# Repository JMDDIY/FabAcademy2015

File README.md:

# FabAcademy2015
'Homework' repository during FAB Academy 2015

if you want to have more information about those files, you should visit my webpage on the 
Fab Academy repository: http://fabacademy.org/archives/2015/eu/students/durney.jean-marie/index.html

All files here are based on Creative Commons
Attribution-NonCommercial-ShareAlike 4.0 International (CC BY-NC-SA 4.0)

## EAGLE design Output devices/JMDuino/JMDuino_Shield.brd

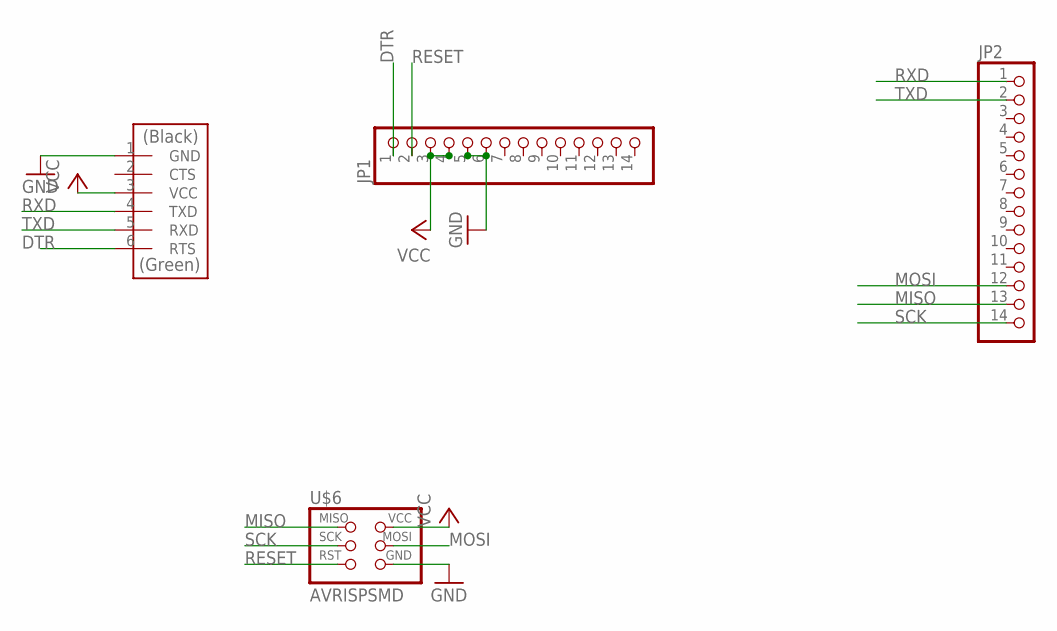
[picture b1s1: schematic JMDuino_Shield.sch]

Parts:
JP1, JP2: PINHD-1X14; 1X14
U$1: FTDI-SMD-HEADER; 1X06SMD
U$6: AVRISPSMD; 2X03SMD

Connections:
DTR: JP1.1, U$1.6 (RTS)
GND: JP1.5, JP1.6, U$1.1 (GND), U$6.6 (GND)
MISO: JP2.13, U$6.1 (MISO)
MOSI: JP2.12, U$6.4 (MOSI)
RESET: JP1.2, U$6.5 (RST)
RXD: JP2.1, U$1.4 (TXD)
SCK: JP2.14, U$6.3 (SCK)
TXD: JP2.2, U$1.5 (RXD)
VCC: JP1.3, JP1.4, U$1.3 (VCC), U$6.2 (VCC)

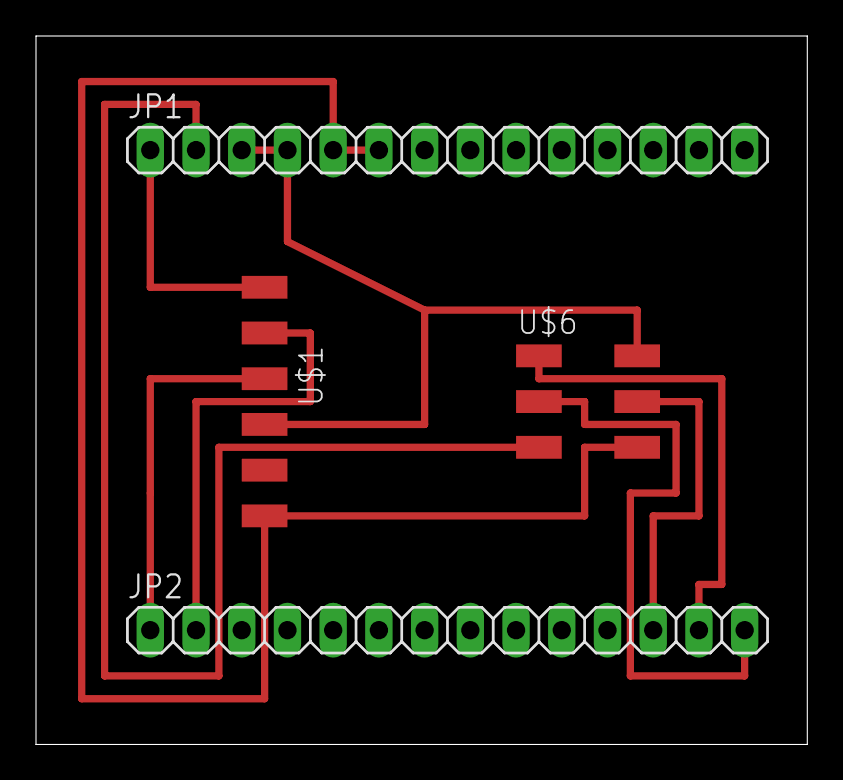
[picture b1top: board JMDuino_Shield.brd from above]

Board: 2 copper layers, 42.9 x 39.4 mm, 4 parts (0 on the bottom side), 9 nets.

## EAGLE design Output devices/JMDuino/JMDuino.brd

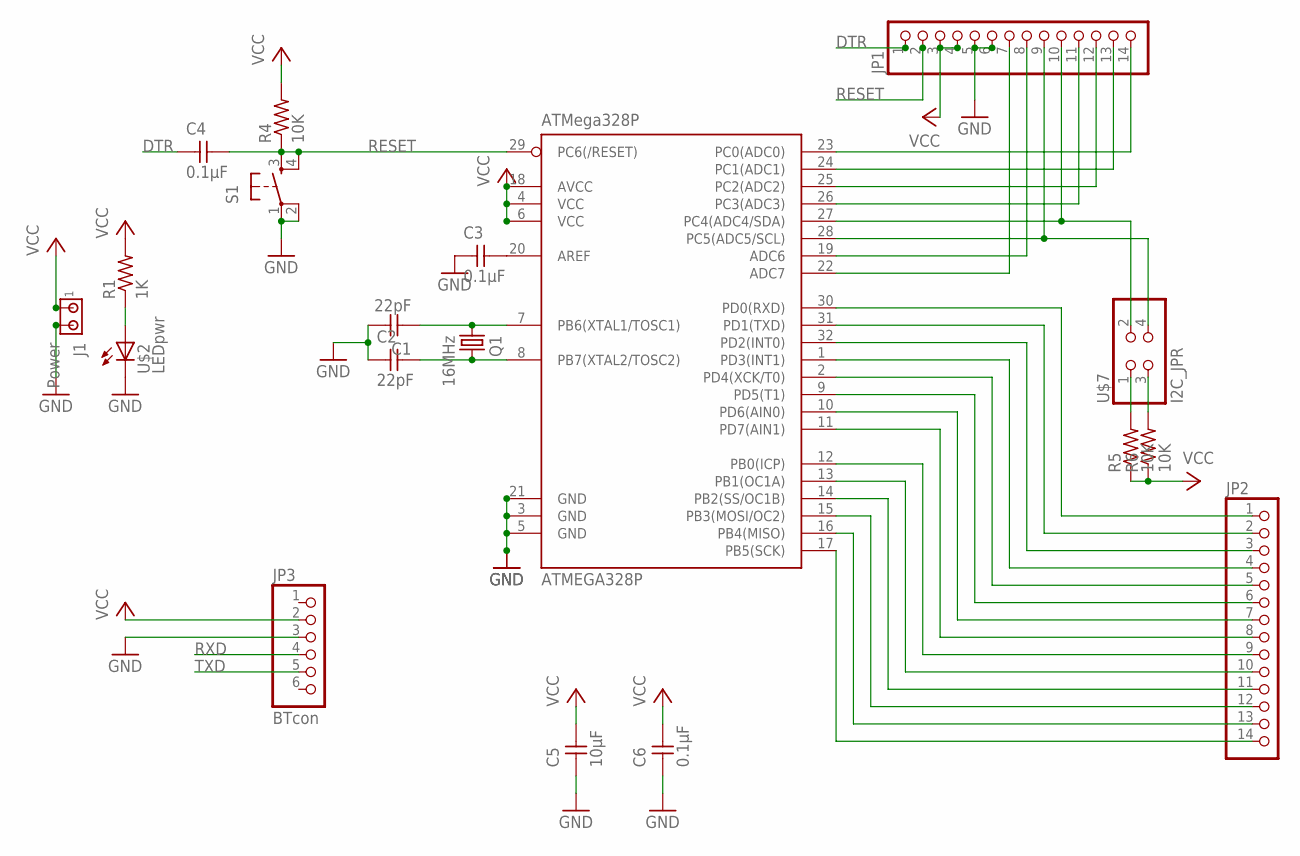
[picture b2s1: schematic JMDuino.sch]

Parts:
ATMEGA328P: ATMega328P; TQFP32-08THIN
C1, C2: 22pF; C1206FAB
C3, C4, C6: 0.1µF; C1206FAB
C5: 10µF; C1206FAB
J1: Power; 350428-1
JP1, JP2: PINHD-1X14; 1X14
JP3: BTcon; 1X06
Q1: 16MHz; 2-SMD-5X3MM
R1: 1K; R1206FAB
R4, R5, R6: 10K; R1206FAB
S1: 6MM_SWITCH6MM_SWITCH; 6MM_SWITCH
U$2: LEDpwr; LED1206FAB
U$7: I2C_JPR; 2X02SMD

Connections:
DTR: C4.1, JP1.1
GND: ATMEGA328P.3 (GND), ATMEGA328P.5 (GND), ATMEGA328P.21 (GND), C1.2, C2.1, C3.1, C5.1, C6.1, J1.2, JP1.5, JP1.6, JP3.3, S1.1, S1.2 (P1), U$2.2 (C)
MISO: ATMEGA328P.16 (PB4(MISO)), JP2.13
MOSI: ATMEGA328P.15 (PB3(MOSI/OC2)), JP2.12
unnamed: ATMEGA328P.23 (PC0(ADC0)), JP1.14
unnamed: ATMEGA328P.24 (PC1(ADC1)), JP1.13
unnamed: ATMEGA328P.25 (PC2(ADC2)), JP1.12
unnamed: ATMEGA328P.26 (PC3(ADC3)), JP1.11
unnamed: ATMEGA328P.20 (AREF), C3.2
unnamed: ATMEGA328P.27 (PC4(ADC4/SDA)), JP1.10, U$7.2
unnamed: ATMEGA328P.9 (PD5(T1)), JP2.6
unnamed: ATMEGA328P.28 (PC5(ADC5/SCL)), JP1.9, U$7.4
unnamed: ATMEGA328P.32 (PD2(INT0)), JP2.3
unnamed: ATMEGA328P.1 (PD3(INT1)), JP2.4
unnamed: ATMEGA328P.2 (PD4(XCK/T0)), JP2.5
unnamed: ATMEGA328P.10 (PD6(AIN0)), JP2.7
unnamed: ATMEGA328P.11 (PD7(AIN1)), JP2.8
unnamed: ATMEGA328P.12 (PB0(ICP)), JP2.9
unnamed: ATMEGA328P.13 (PB1(OC1A)), JP2.10
unnamed: ATMEGA328P.14 (PB2(SS/OC1B)), JP2.11
unnamed: R1.1, U$2.1 (A)
unnamed: R5.2, U$7.1
unnamed: ATMEGA328P.7 (PB6(XTAL1/TOSC1)), C1.1, Q1.P$1 (1)
unnamed: ATMEGA328P.8 (PB7(XTAL2/TOSC2)), C2.2, Q1.P$2 (2)
unnamed: ATMEGA328P.19 (ADC6), JP1.8
unnamed: R6.2, U$7.3
unnamed: ATMEGA328P.22 (ADC7), JP1.7
RESET: ATMEGA328P.29 (PC6(/RESET)), C4.2, JP1.2, R4.1, S1.4 (S1)
RXD: ATMEGA328P.30 (PD0(RXD)), JP2.1, JP3.4
SCK: ATMEGA328P.17 (PB5(SCK)), JP2.14
TXD: ATMEGA328P.31 (PD1(TXD)), JP2.2, JP3.5
VCC: ATMEGA328P.4 (VCC), ATMEGA328P.6 (VCC), ATMEGA328P.18 (AVCC), C5.2, C6.2, J1.1, JP1.3, JP1.4, JP3.2, R1.2, R4.2, R5.1, R6.1

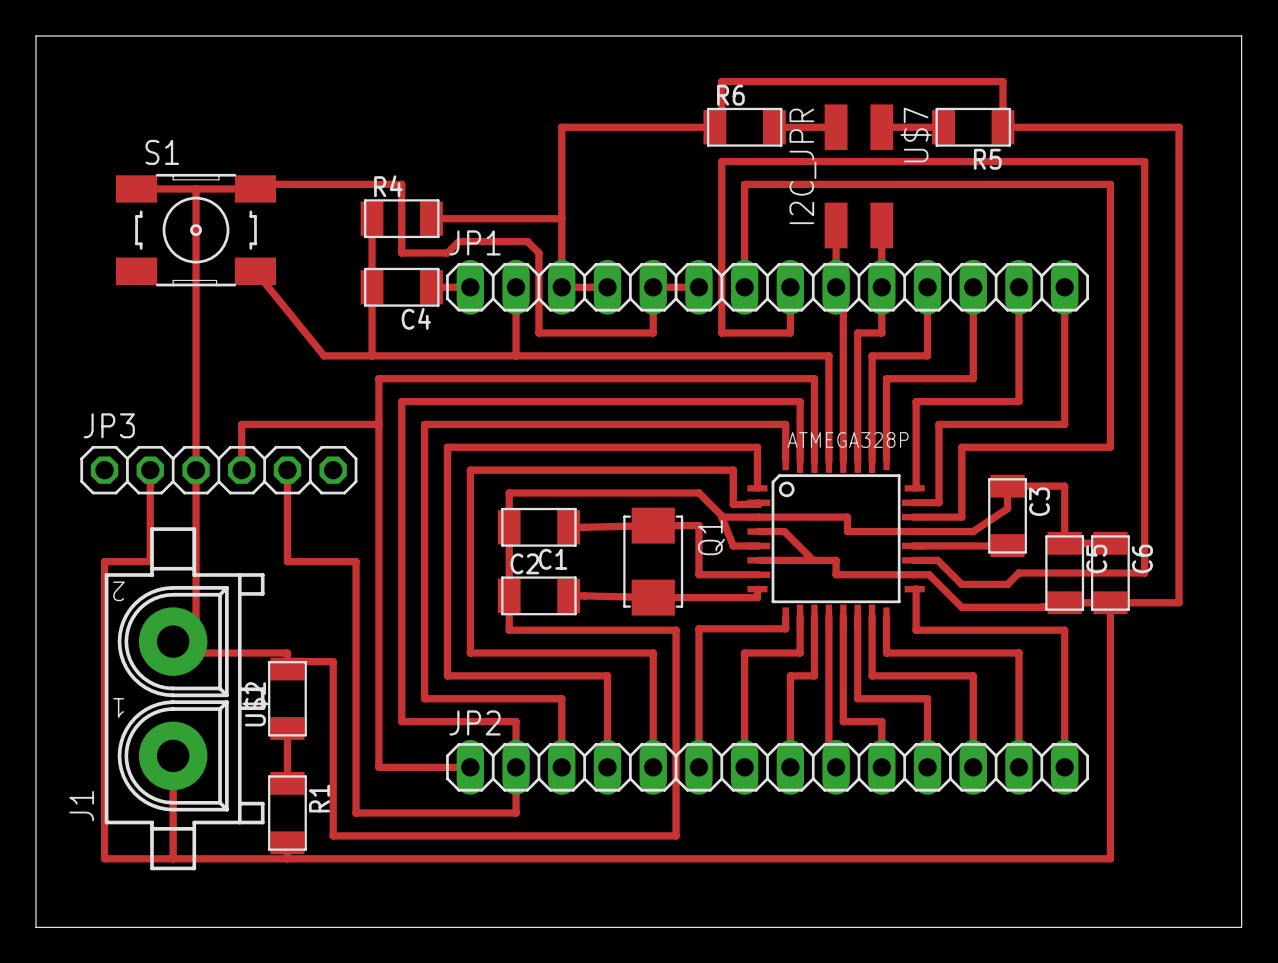
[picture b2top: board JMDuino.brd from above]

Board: 2 copper layers, 67.0 x 49.5 mm, 19 parts (0 on the bottom side), 32 nets.

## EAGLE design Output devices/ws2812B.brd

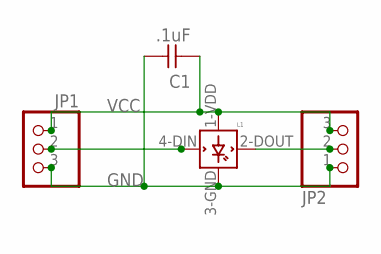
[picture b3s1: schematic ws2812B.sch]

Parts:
C1: .1uF; C1206FAB
JP1, JP2: PINHD-1X3CB; 1X03-CLEANBIG
L1: WS2812B

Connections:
GND: C1.2, JP1.3, JP2.1, L1.3-GND (GND)
unnamed: JP2.2, L1.2-DOUT (DOUT)
unnamed: JP1.2, L1.4-DIN (DIN)
VCC: C1.1, JP1.1, JP2.3, L1.1-VDD (VDD)

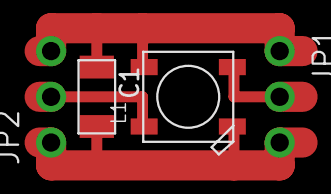
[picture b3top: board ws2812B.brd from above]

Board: 2 copper layers, 4 parts (0 on the bottom side), 4 nets.

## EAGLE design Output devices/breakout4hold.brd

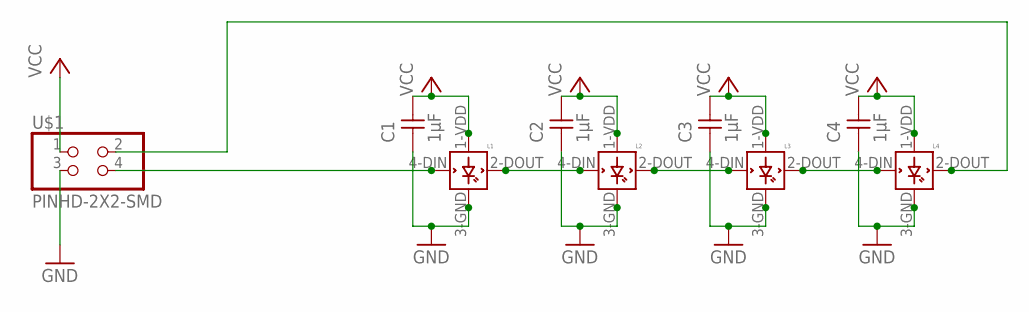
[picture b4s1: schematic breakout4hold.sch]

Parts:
C1, C2, C3, C4: 1µF; C1206FAB
L1, L2, L3, L4: WS2812B
U$1: PINHD-2X2-SMD; 2X02SMD

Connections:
GND: C1.1, C2.1, C3.1, C4.1, L1.3-GND (GND), L2.3-GND (GND), L3.3-GND (GND), L4.3-GND (GND), U$1.3
unnamed: L4.2-DOUT (DOUT), U$1.2
unnamed: L1.4-DIN (DIN), U$1.4
unnamed: L1.2-DOUT (DOUT), L2.4-DIN (DIN)
unnamed: L2.2-DOUT (DOUT), L3.4-DIN (DIN)
unnamed: L3.2-DOUT (DOUT), L4.4-DIN (DIN)
VCC: C1.2, C2.2, C3.2, C4.2, L1.1-VDD (VDD), L2.1-VDD (VDD), L3.1-VDD (VDD), L4.1-VDD (VDD), U$1.1

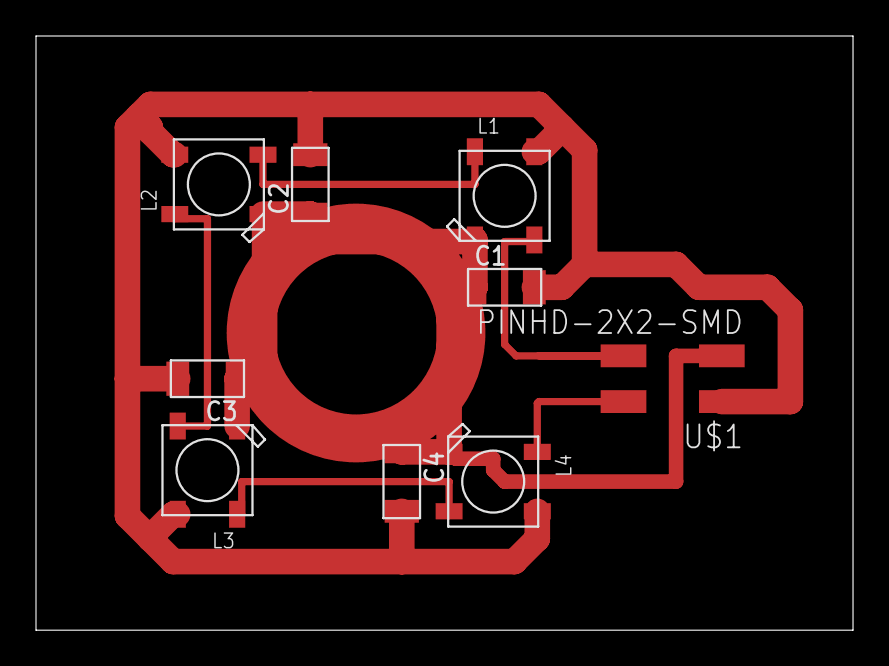
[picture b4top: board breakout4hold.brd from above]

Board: 2 copper layers, 45.4 x 33.0 mm, 9 parts (0 on the bottom side), 7 nets.

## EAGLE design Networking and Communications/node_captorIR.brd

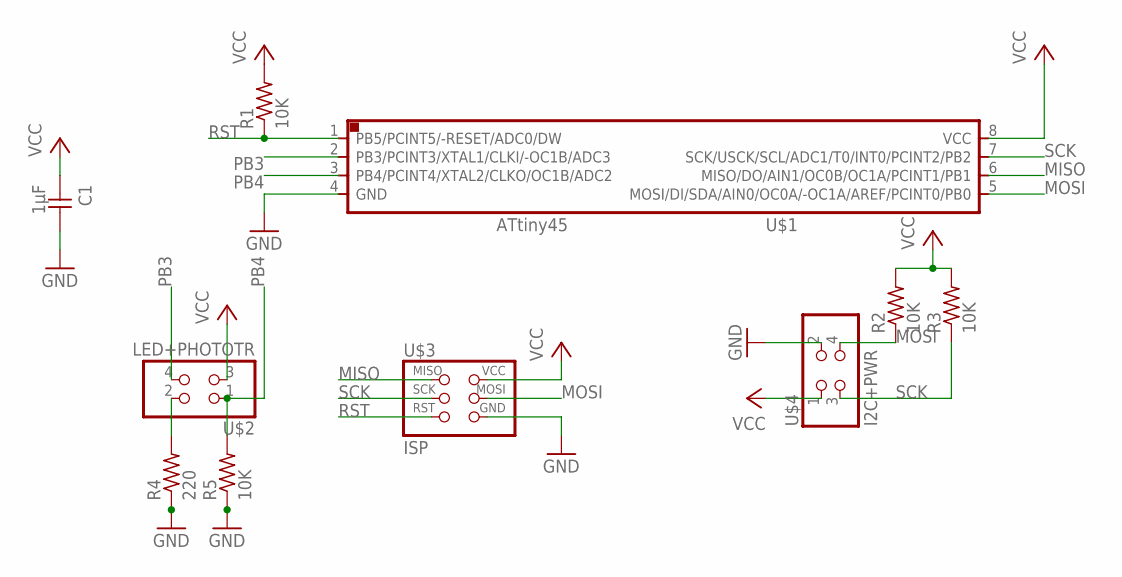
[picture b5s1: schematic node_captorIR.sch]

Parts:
C1: 1µF; C1206FAB
R1, R2, R3, R5: 10K; R1206FAB
R4: 220; R1206FAB
U$1: ATTINY45SI; SOIC8
U$2: LED+PHOTOTR; 2X02SMD
U$3: ISP; 2X03SMD
U$4: I2C+PWR; 2X02SMD

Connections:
GND: C1.2, R4.1, R5.1, U$1.4 (GND), U$3.6 (GND), U$4.2
MISO: U$1.6 (MISO/DO/AIN1/OC0B/OC1A/PCINT1/PB1), U$3.1 (MISO)
MOSI: R2.1, U$1.5 (MOSI/DI/SDA/AIN0/OC0A/-OC1A/AREF/PCINT0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), U$3.4 (MOSI), U$4.4
unnamed: R4.2, U$2.2
PB3: U$1.2 (PB3/PCINT3/XTAL1/CLKI/-OC1B/ADC3), U$2.4
PB4: R5.2, U$1.3 (PB4/PCINT4/XTAL2/CLKO/OC1B/ADC2), U$2.1
RST: R1.1, U$1.1 (PB5/PCINT5/-RESET/ADC0/DW), U$3.5 (RST)
SCK: R3.1, U$1.7 (SCK/USCK/SCL/ADC1/T0/INT0/PCINT2/PB2), U$3.3 (SCK), U$4.3
VCC: C1.1, R1.2, R2.2, R3.2, U$1.8 (VCC), U$2.3, U$3.2 (VCC), U$4.1

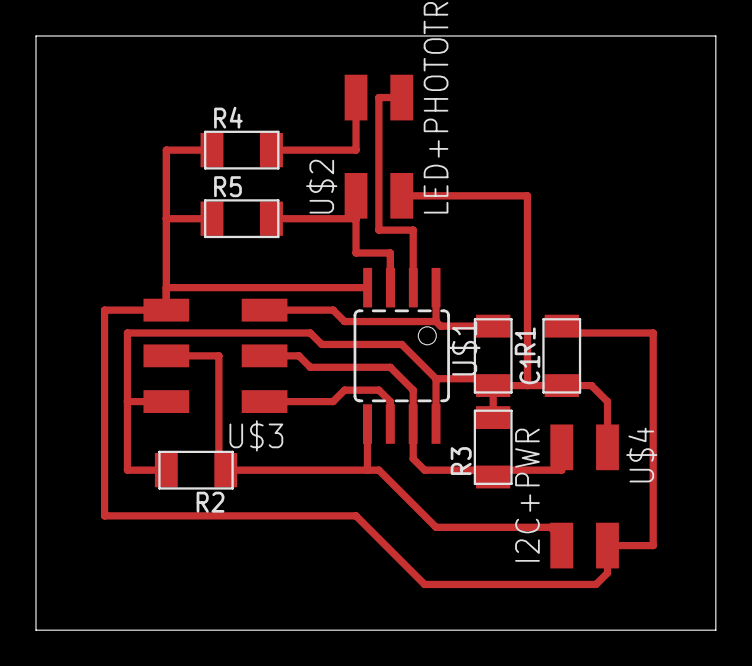
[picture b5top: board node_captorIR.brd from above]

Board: 2 copper layers, 37.8 x 33.0 mm, 10 parts (0 on the bottom side), 9 nets.

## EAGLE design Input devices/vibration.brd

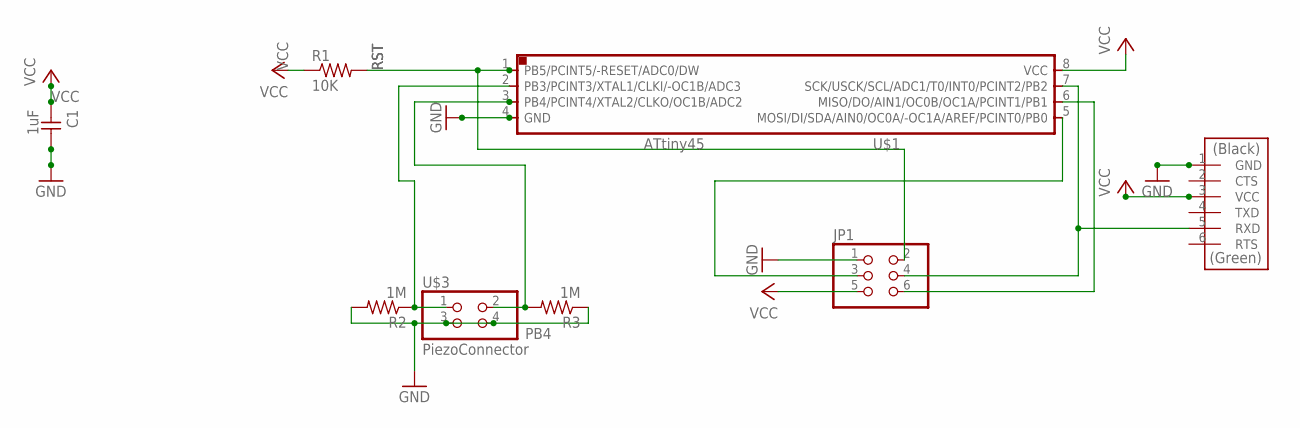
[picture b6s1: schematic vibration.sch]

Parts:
C1: 1uF; C1206FAB
JP1: PINHD-2X3-SMD; 2X03SMD
R1: 10K; R1206FAB
R2, R3: 1M; R1206FAB
U$1: ATTINY45SI; SOIC8
U$2: FTDI-SMD-HEADER; 1X06SMD
U$3: PiezoConnector; 2X02SMD

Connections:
GND: C1.2, JP1.1, R2.2, R3.1, U$1.4 (GND), U$2.1 (GND), U$3.3, U$3.4
unnamed: R2.1, U$1.2 (PB3/PCINT3/XTAL1/CLKI/-OC1B/ADC3), U$3.1
unnamed: JP1.6, U$1.6 (MISO/DO/AIN1/OC0B/OC1A/PCINT1/PB1)
unnamed: JP1.4, U$1.7 (SCK/USCK/SCL/ADC1/T0/INT0/PCINT2/PB2), U$2.5 (RXD)
unnamed: JP1.3, U$1.5 (MOSI/DI/SDA/AIN0/OC0A/-OC1A/AREF/PCINT0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)
PB4: R3.2, U$1.3 (PB4/PCINT4/XTAL2/CLKO/OC1B/ADC2), U$3.2
RST: JP1.2, R1.2, U$1.1 (PB5/PCINT5/-RESET/ADC0/DW)
VCC: C1.1, JP1.5, R1.1, U$1.8 (VCC), U$2.3 (VCC)

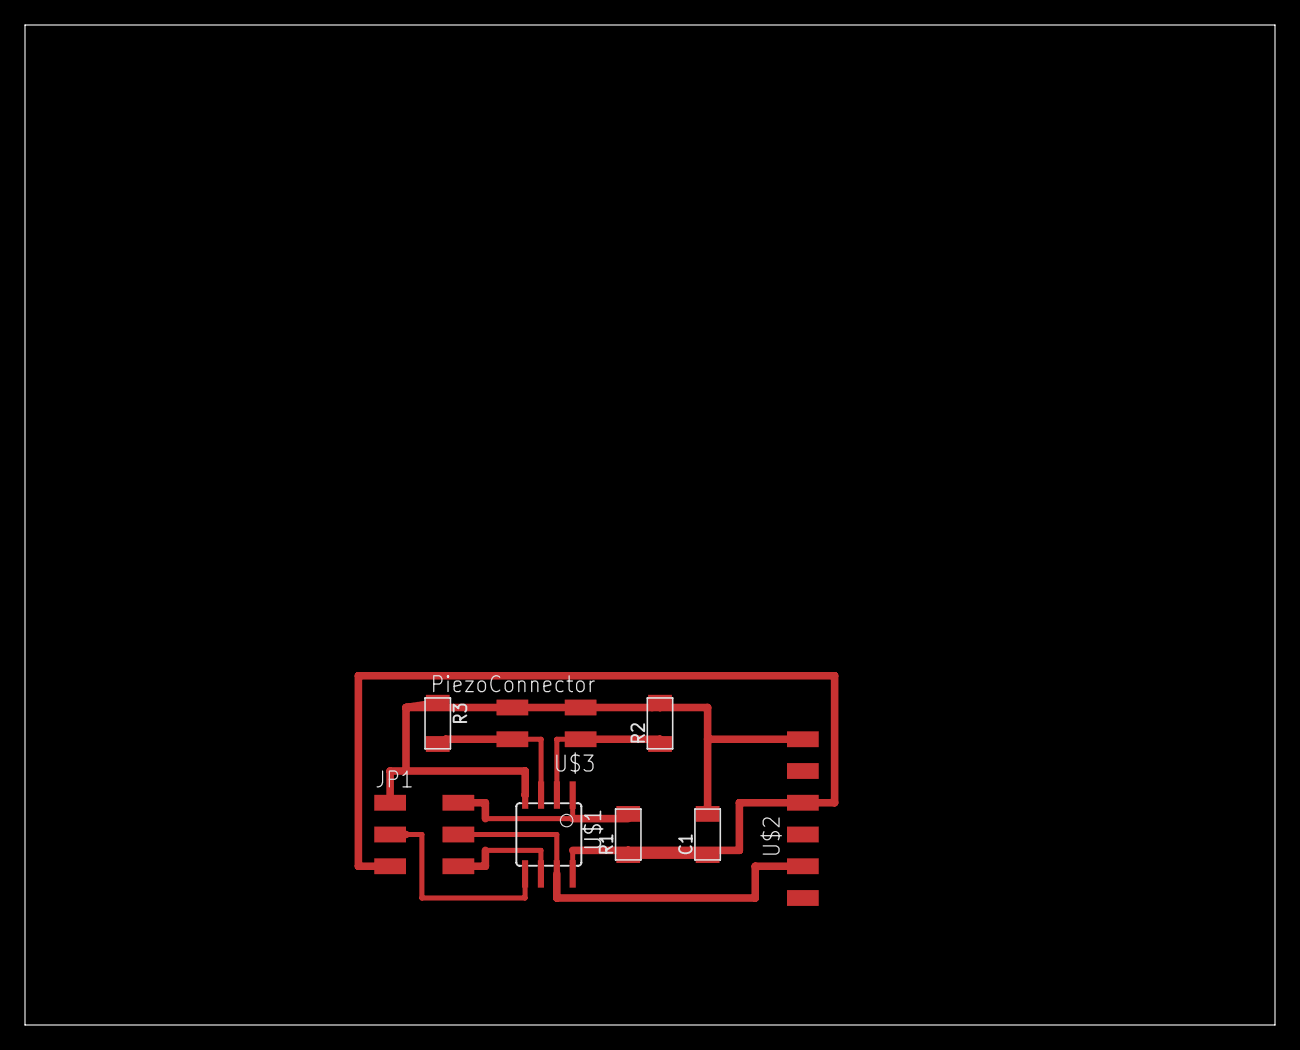
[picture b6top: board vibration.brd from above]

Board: 2 copper layers, 100.0 x 80.0 mm, 8 parts (0 on the bottom side), 8 nets.

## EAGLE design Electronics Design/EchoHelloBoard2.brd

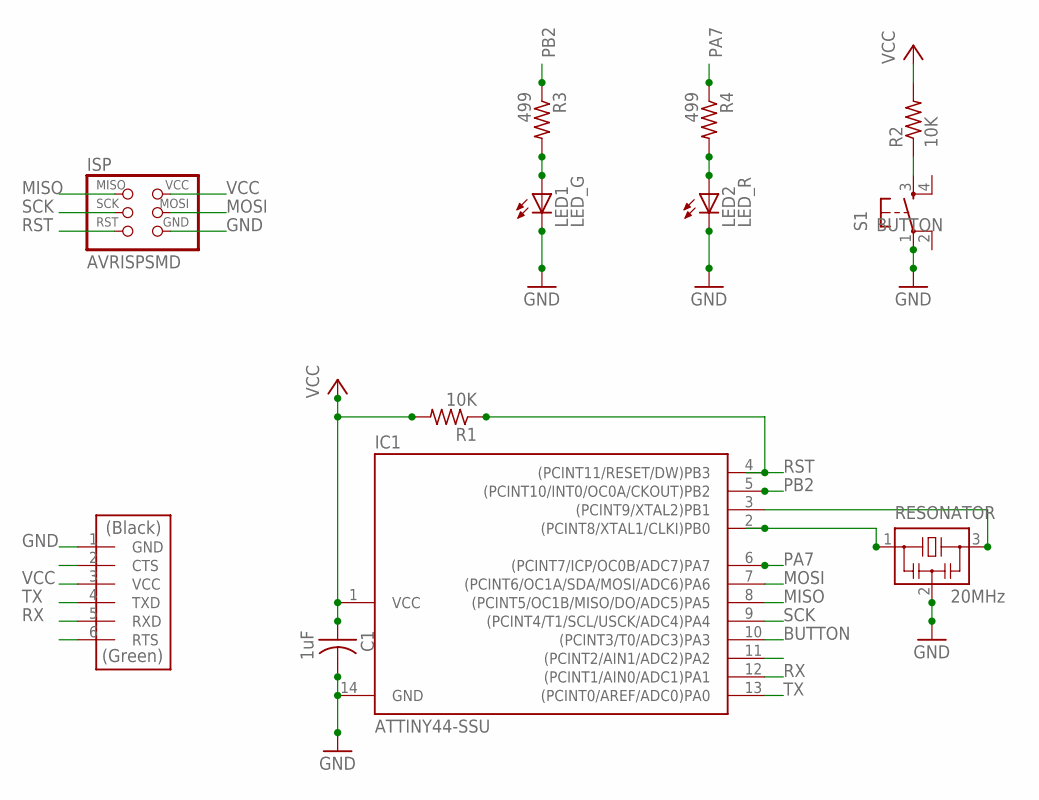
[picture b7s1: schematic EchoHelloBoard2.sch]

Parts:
C1: 1uF; C1206FAB
IC1: ATTINY44-SSU; SOIC14
ISP: AVRISPSMD; 2X03SMD
LED1: LED_G; LED1206FAB
LED2: LED_R; LED1206FAB
R1, R2: 10K; R1206FAB
R3, R4: 499; R1206FAB
RESONATOR: 20MHz; EFOBM
S1: 6MM_SWITCH6MM_SWITCH; 6MM_SWITCH
U$2: FTDI-SMD-HEADER; 1X06SMD

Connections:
BUTTON: IC1.10 ((PCINT3/T0/ADC3)PA3), R2.1, S1.3 (S)
GND: C1.2, IC1.14 (GND), ISP.6 (GND), LED1.2 (C), LED2.2 (C), RESONATOR.2, S1.1, U$2.1 (GND)
MISO: IC1.8 ((PCINT5/OC1B/MISO/DO/ADC5)PA5), ISP.1 (MISO)
MOSI: IC1.7 ((PCINT6/OC1A/SDA/MOSI/ADC6)PA6), ISP.4 (MOSI)
unnamed: IC1.3 ((PCINT9/XTAL2)PB1), RESONATOR.3
unnamed: IC1.2 ((PCINT8/XTAL1/CLKI)PB0), RESONATOR.1
unnamed: LED1.1 (A), R3.2
unnamed: LED2.1 (A), R4.2
PA7: IC1.6 ((PCINT7/ICP/OC0B/ADC7)PA7), R4.1
PB2: IC1.5 ((PCINT10/INT0/OC0A/CKOUT)PB2), R3.1
RST: IC1.4 ((PCINT11/RESET/DW)PB3), ISP.5 (RST), R1.1
RX: IC1.12 ((PCINT1/AIN0/ADC1)PA1), U$2.5 (RXD)
SCK: IC1.9 ((PCINT4/T1/SCL/USCK/ADC4)PA4), ISP.3 (SCK)
TX: IC1.13 ((PCINT0/AREF/ADC0)PA0), U$2.4 (TXD)
VCC: C1.1, IC1.1 (VCC), ISP.2 (VCC), R1.2, R2.2, U$2.3 (VCC)

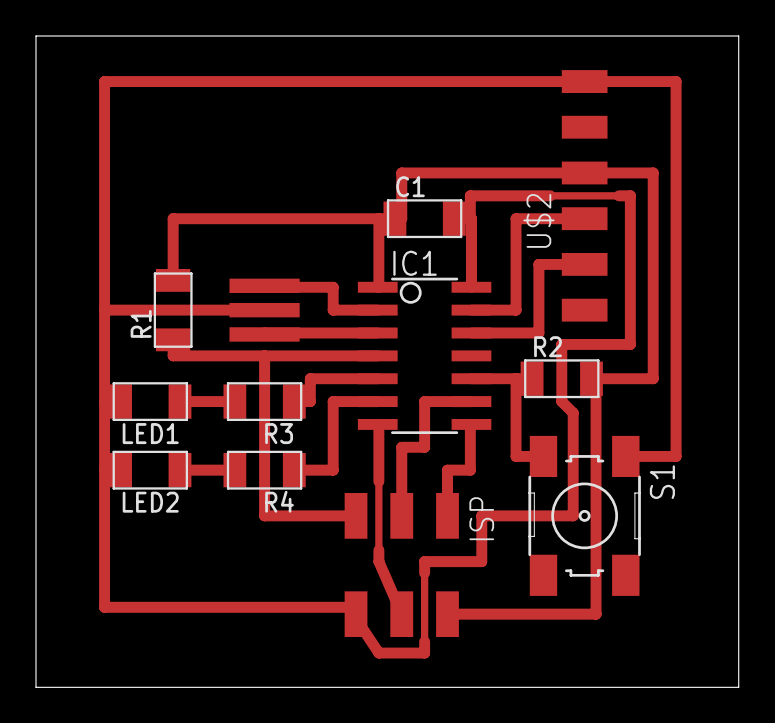
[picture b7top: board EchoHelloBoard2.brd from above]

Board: 2 copper layers, 39.0 x 36.2 mm, 12 parts (0 on the bottom side), 15 nets.

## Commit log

2015-06-16 Molding and casting
    source file (Rhino 5)
2015-06-16 big update
    folder & subfolders creation
2015-06-17 update 3d scanning
2015-06-17 update elec design
2015-06-18 Update input devices
2015-06-18 Week11 update
2015-06-18 code week10
2015-06-21 output devices update
2015-06-21 remove unnecessary files
2015-06-28 networking update
2015-06-28 interface programming
2015-06-30 design files
2015-06-30 mechanical design update
2015-07-01 data only in project
2015-07-01 program
